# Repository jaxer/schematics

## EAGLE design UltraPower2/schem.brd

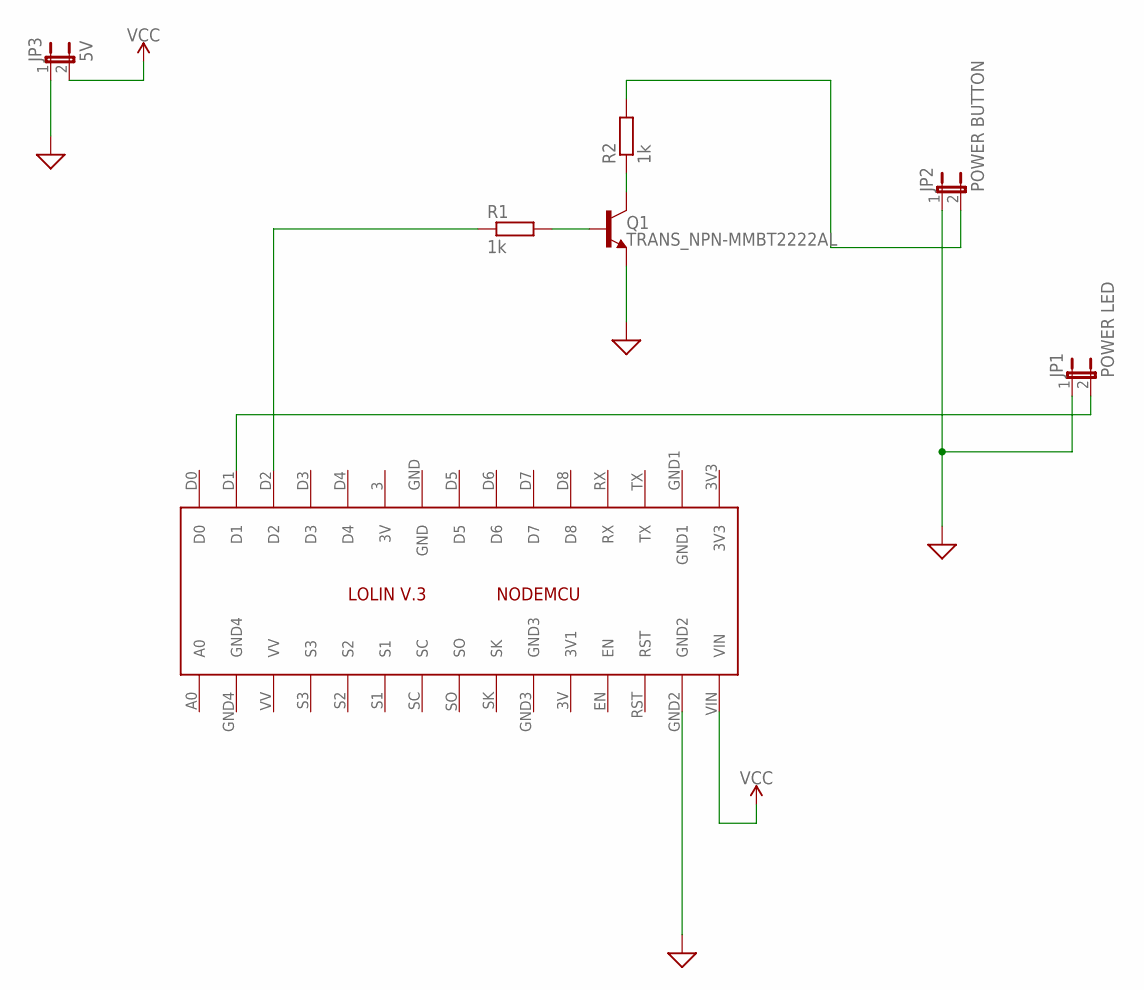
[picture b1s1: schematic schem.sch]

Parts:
IC1: LOLINV3
JP1: POWER LED; JP1
JP2: POWER BUTTON; JP1
JP3: 5V; JP1
Q1: TRANS_NPN-MMBT2222AL; SOT23-3
R1, R2: 1k; M0805

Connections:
GND: IC1.GND2, JP1.1, JP2.1, JP3.1, Q1.2 (E)
unnamed: IC1.D1, JP1.2
unnamed: IC1.D2, R1.1
unnamed: Q1.1 (B), R1.2
unnamed: Q1.3 (C), R2.1
unnamed: JP2.2, R2.2
VCC: IC1.VIN, JP3.2

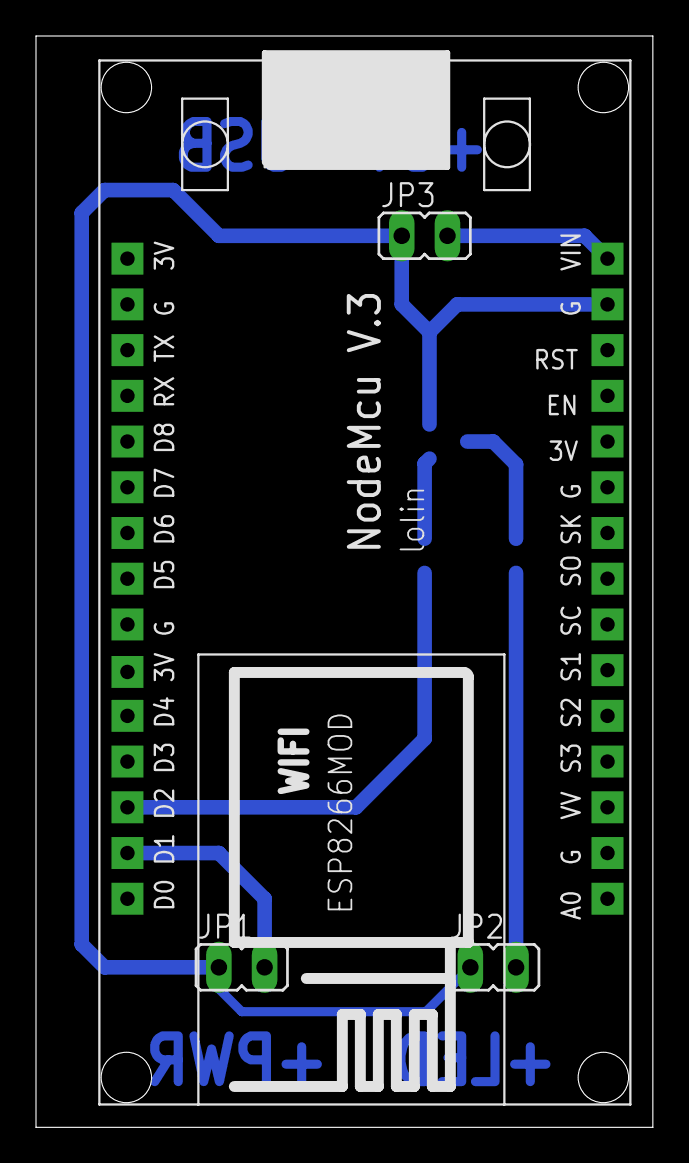
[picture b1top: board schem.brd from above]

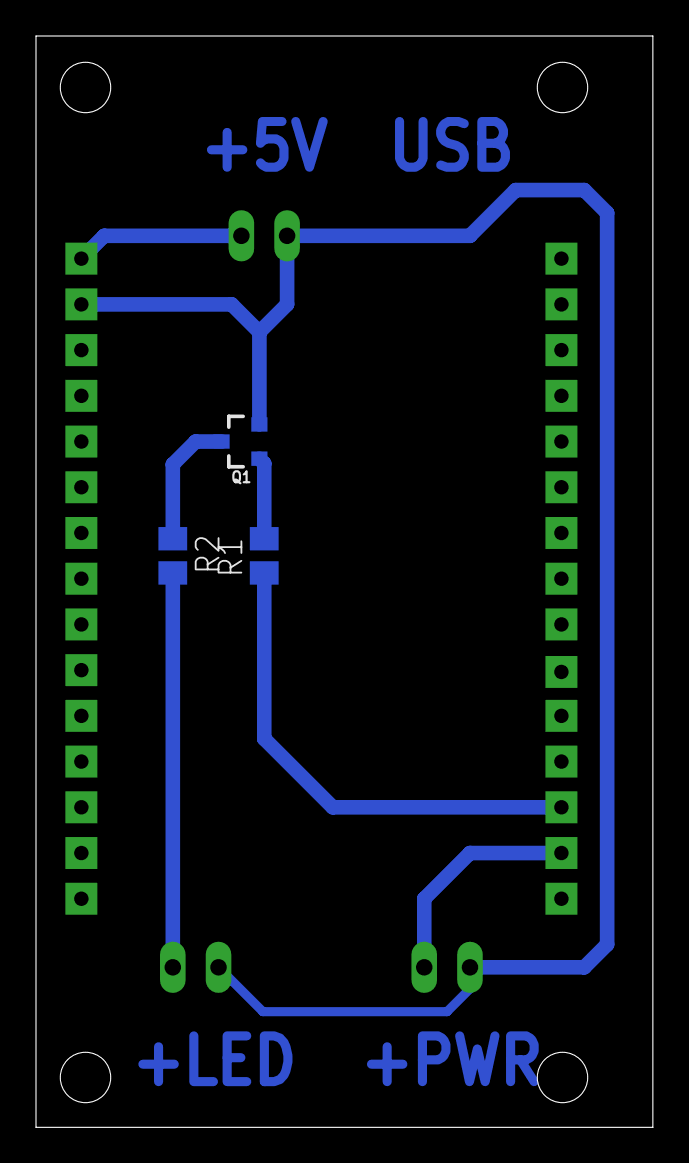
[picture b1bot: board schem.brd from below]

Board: 2 copper layers, 34.3 x 60.6 mm, 7 parts (3 on the bottom side), 7 nets.

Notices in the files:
parts and their libraries:
SparkFun-DiscreteSemi: Licensing: Creative Commons ShareAlike 4.0 International - https://creativecommons.org/licenses/by-sa/4.0
